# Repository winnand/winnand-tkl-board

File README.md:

# The Winnand TKL Keyboard

This project is a custom keyboard based off of JoeScotto's guides from YouTube. It is a standard TKL Board which replaces the Pause key with a rotary encoder. It uses QMK with Vial support for on-the-go layout customization.

I made this project because I enjoyed the idea of having a keyboard that I made myself, with the features and rigidity of a top-of-the-line keyboard. I hoped that it would teach me more about firmware and microcontrollers for future projects, and have a good keyboard that I would be able to use for many years to come. 

# BOM

|Part #                                    |Min. Quantity |Name on Seller Website                                                                                                          |Description      |Link                                                  |Color/Size                                                 |Quantity|Unit Price ($)|Total Price ($)|Running Total ($)|
|------------------------------------------|--------------|--------------------------------------------------------------------------------------------------------------------------------|-----------------|------------------------------------------------------|-----------------------------------------------------------|--------|--------------|---------------|-----------------|
|MX-keyboard switches                      |86            |Outemu Switch Mechanical Keyboard Switch 3Pin Clicky Linear Tactile Silent Switches RGB LED SMD Gaming Compatible With MX Switch|Keyboard Switches|https://www.aliexpress.us/item/3256802192387196.html  |Color: Dust-Proof Purple Axis Body: 90PCS                  |1       |$10.31        |$10.31         |$10.31           |
|Red LED                                   |87            |100pcs 5mm LED Diode F5 Assorted Kit White Green Red Blue Yellow Orange Pink Purple Warm White DIY Light Emitting Diode         |Diodes           |https://www.aliexpress.us/item/3256806276743323.html  |Color: Red-Red                                             |1       |$2.19         |$2.19          |$12.50           |
|EC11 Rotary Encoder                       |1             |5PCS/LOT 20 Position 360 Degree Rotary Encoder EC11 w Push Button 5Pin Handle Long 15/20MM With A Built In Push Button Switch   |Rotary Encoder   |https://www.aliexpress.us/item/3256805796819763.html? |15MM Half handle                                           |1       |$3.30         |$3.30          |$15.80           |
|Raspberry Pi Pico                         |1             |Raspberry Pi Pico                                                                                                               |Microcontroller  |https://www.sparkfun.com/raspberry-pi-pico.html       |                                                           |0       |$4.60         |$0.00          |$15.80           |
|Micro USB male to panel mount USB C female|1             |USB 3.1 Type C Micro Usb2.0 With Panel Mount Screw Extension Cable Cord USB C Male To Female Extending Wire Extender Data Cord  |Adapter Cable    |https://www.aliexpress.us/item/3256806244885684.html  |A3                                                         |1       |$2.69         |$2.69          |$18.49           |
|M2 x 6mm Button Head screw                |11            |10/50pcs M1.6 M2 M2.5 M3 M4 M5 M6 M8 Black Grade 10.9 Steel ISO7380 Hexagon Hex Socket Head Button Mushroom Allen Bolt Screw    |Mounting Screws  |https://www.aliexpress.us/item/2251832782727837.html  |Size: M2 (50pcs) Length: 6mm                               |1       |$1.07         |$1.07          |$19.56           |
|MX Keycaps                                |TKL Layout    |104pcs ABS Universal Mechanical Keyboard Keycaps Ergonomic Blank Keycaps For Cherry MX Keyboard Replacement OEM Backlit Key Cap |Keycaps          |https://www.aliexpress.us/item/3256808802544300.html  |Red black                                                  |1       |$11.48        |$11.48         |$31.04           |
|Plate Mount Stabilizers                   |1x 6.25U 4x 2U|KEYCOOL V3 PCB Plate Mounted Stabilizer for Gaming Mechanical Keyboard Lubrication Satellite Switches for 1.2mm 1.6mm PCB 6.25U |Stabilizers      |https://www.aliexpress.us/item/3256808467378574.html  |Black 4 in 1                                               |1       |$3.01         |$3.01          |$34.05           |
|M2, OD4mm Heatset Inserts                 |11            |M2 M2.5 M3 M4 M5 M6 Brass Hot Melt Insert Knurled Nut Thread Heat Molding Double Twill Injection Embedment Nut For 3D Printer   |Heatset Inserts  |https://www.aliexpress.us/item/3256803396040989.html  |Size: M2(OD4mm)  Color: Length 5mm 50pcs                   |1       |$2.27         |$2.27          |$36.32           |
|Winnand-TKL PCB                           |1             |JLCPCB                                                                                                                          |PCB              |https://cart.jlcpcb.com/quote?spm=Jlcpcb.Homepage.1006|Defaults except: PCB Color: Black Via Covering: Untented   |5       |$4.16         |$20.80         |$57.12           |
|ARGB lights                               |1             |Addressable ARGB 5V LED Strip 3Pin Computer PC Case Tape Light WS2812B SMD 5050 Flexible Changeable Color Gamer Desktop Lamp    |Lights           |https://www.aliexpress.us/item/3256802938234249.html? |Emitting Color: 1 x 0.5m 30leds  Color: IP30 Non waterproof|1       |$4.00         |$4.00          |$61.12           |

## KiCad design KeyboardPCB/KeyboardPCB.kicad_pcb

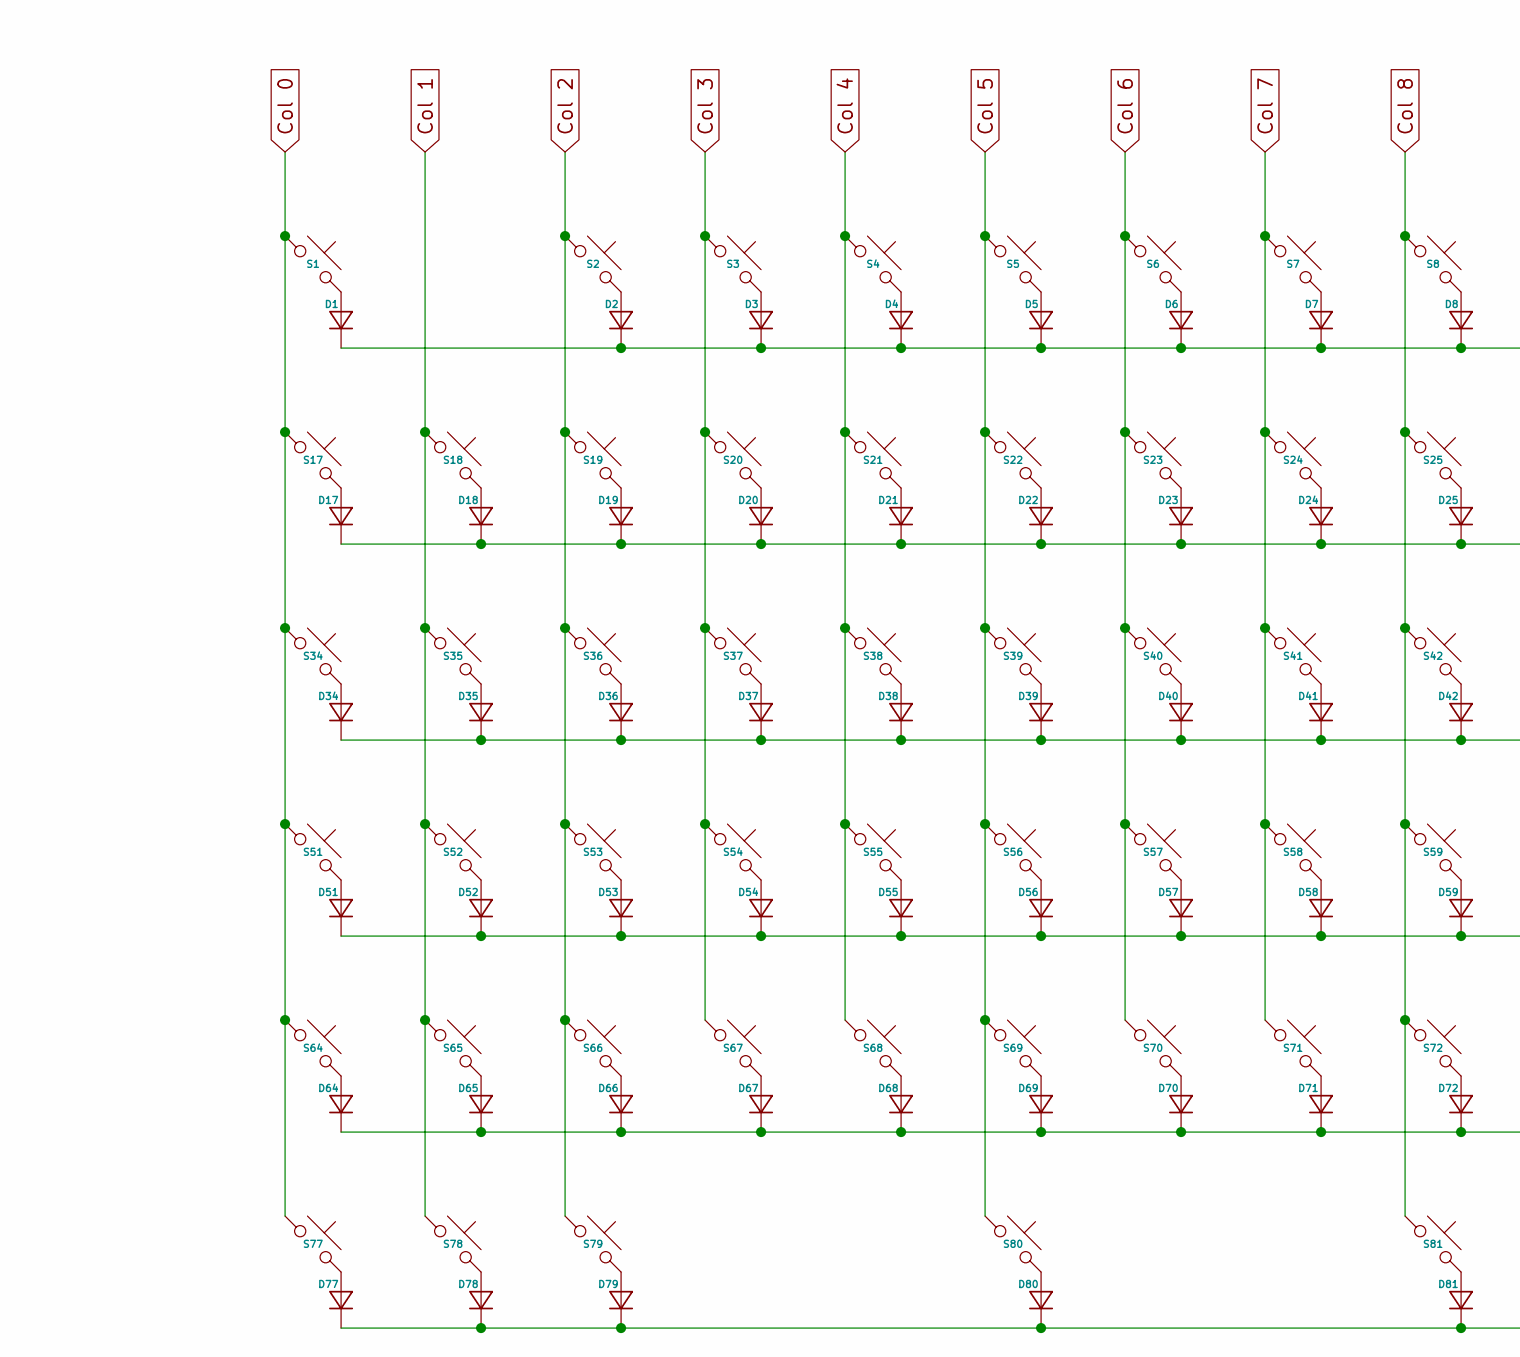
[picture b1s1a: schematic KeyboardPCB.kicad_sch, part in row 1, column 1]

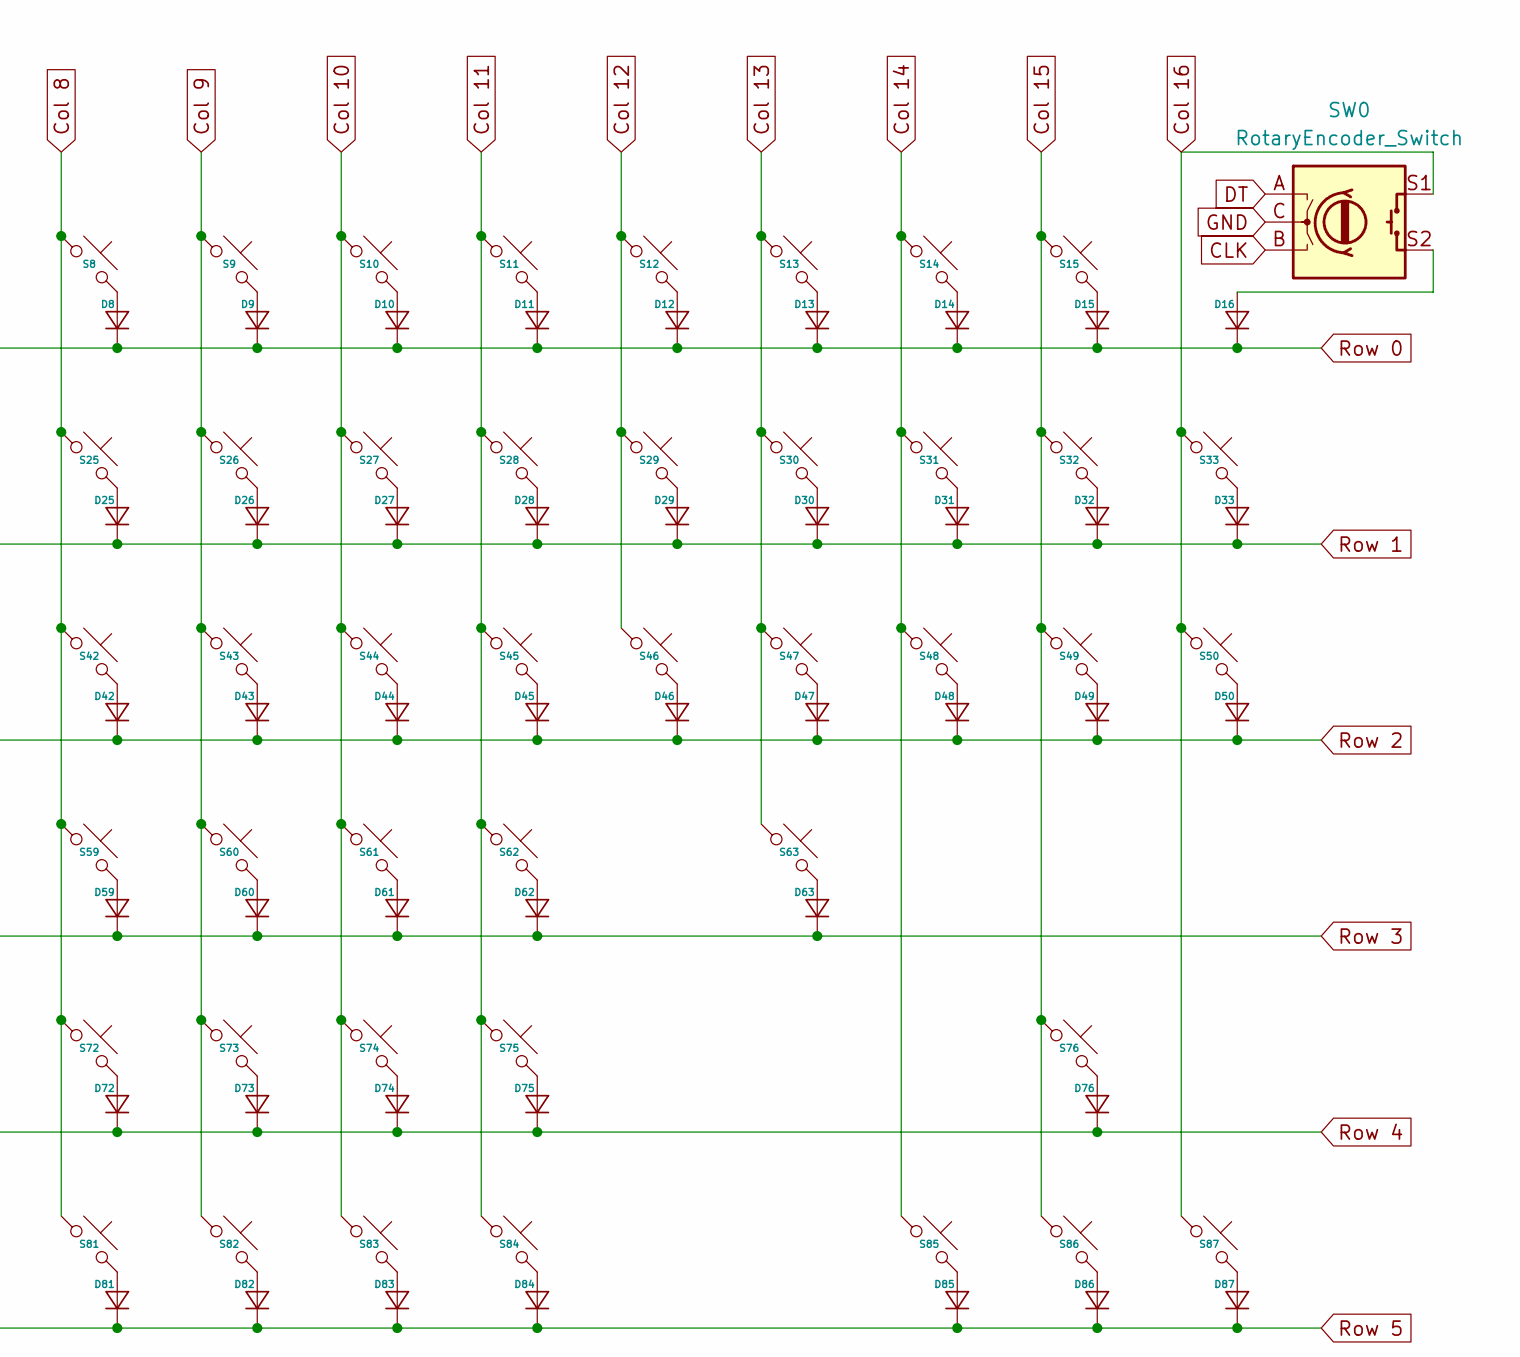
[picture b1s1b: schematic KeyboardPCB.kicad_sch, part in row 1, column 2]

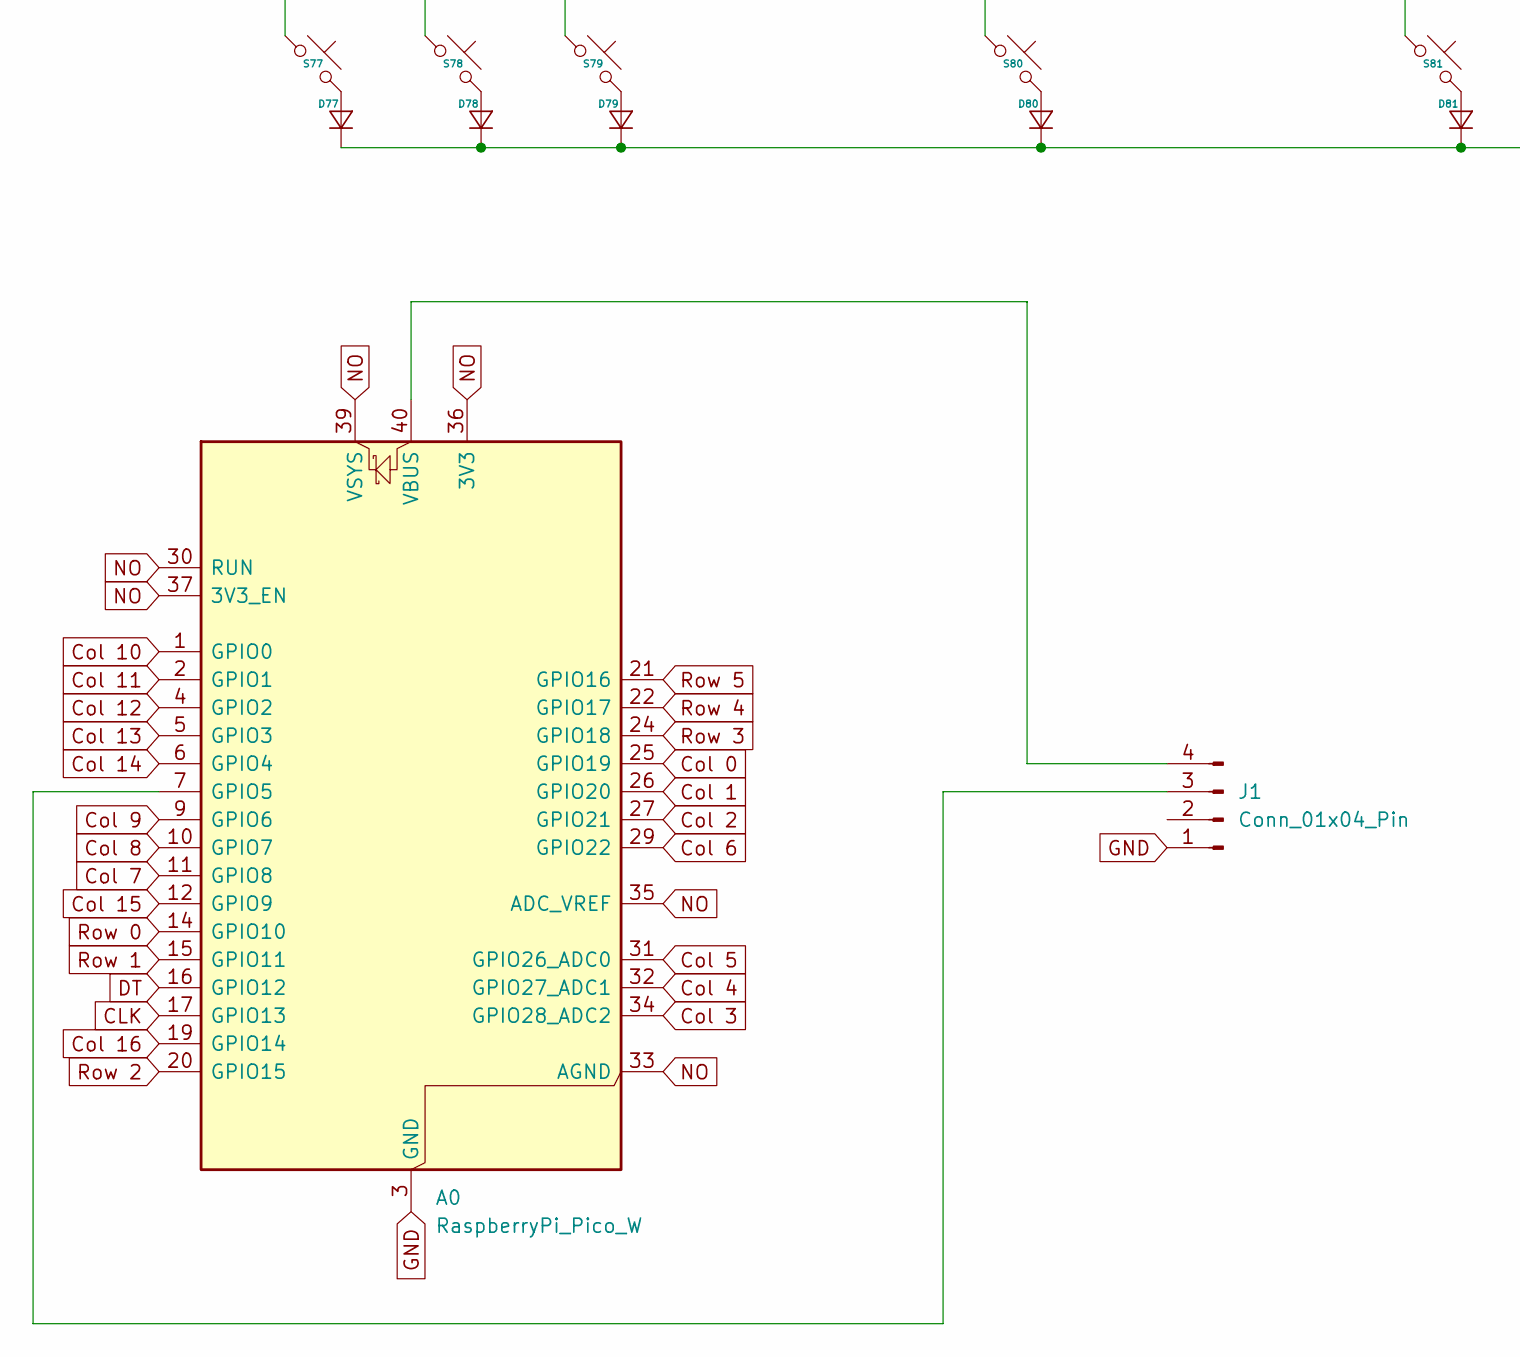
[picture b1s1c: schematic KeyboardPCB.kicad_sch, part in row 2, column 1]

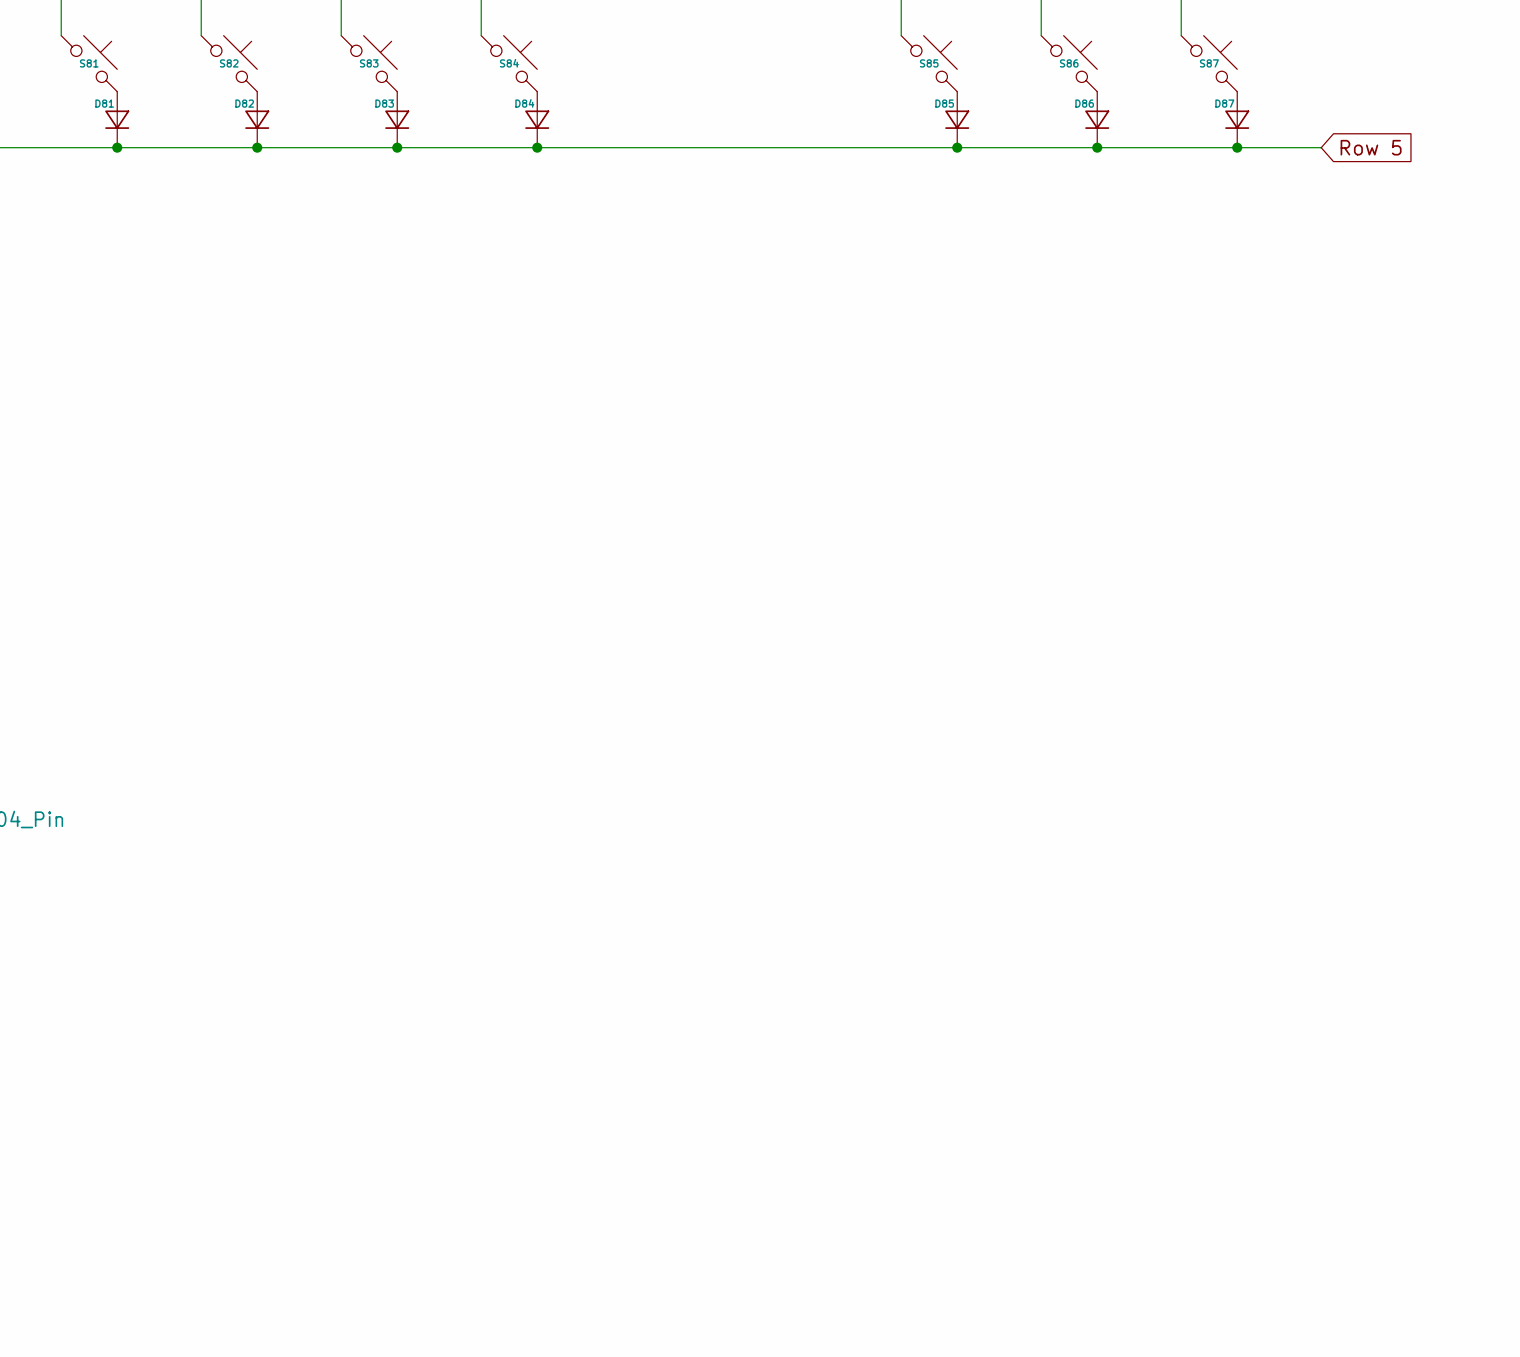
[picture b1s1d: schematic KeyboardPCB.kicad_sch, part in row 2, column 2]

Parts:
A0: RaspberryPi_Pico_W; RaspberryPi_Pico_W_SMD_HandSolder
D1, D2, D3, D4, D5, D6, D7, D8, D9, D10, D11, D12, D13, D14, D15, D16, D17, D18, D19, D20, D21, D22, D23, D24, D25, D26, D27, D28, D29, D30, D31, D32, D33, D34, D35, D36, D37, D38, D39, D40, D41, D42, D43, D44, D45, D46, D47, D48, D49, D50, D51, D52, D53, D54, D55, D56, D57, D58, D59, D60, D61, D62, D63, D64, D65, D66, D67, D68, D69, D70, D71, D72, D73, D74, D75, D76, D77, D78, D79, D80, D81, D82, D83, D84, D85, D86, D87: Diode_DO-35
J1: Conn_01x04_Pin; PinHeader_1x04_P2.54mm_Vertical
S1, S2, S3, S4, S5, S6, S7, S8, S9, S10, S11, S12, S13, S14, S15, S17, S18, S19, S20, S21, S22, S23, S24, S25, S26, S27, S28, S29, S31, S32, S33, S35, S36, S37, S38, S39, S40, S41, S42, S43, S44, S45, S46, S48, S49, S50, S52, S53, S54, S55, S56, S57, S58, S59, S60, S61, S62, S65, S66, S67, S68, S69, S70, S71, S72, S73, S74, S76, S85, S86, S87: MX_PCB_1.00u
S30: MX_PCB_2.00u
S34, S47: MX_PCB_1.50u
S51: MX_PCB_1.75u
S63, S64: MX_PCB_2.25u
S75: MX_PCB_2.75u
S77, S78, S79, S81, S82, S83, S84: MX_PCB_1.25u
S80: MX_PCB_6.25u
SW0: RotaryEncoder_Switch; Encoder_EC11_MX

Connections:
CLK: A0.17 (GPIO13), SW0.B
Col 0: A0.25 (GPIO19), S1.1, S17.1, S34.1, S51.1, S64.1, S77.1
Col 1: A0.26 (GPIO20), S18.1, S35.1, S52.1, S65.1, S78.1
Col 2: A0.27 (GPIO21), S2.1, S19.1, S36.1, S53.1, S66.1, S79.1
Col 3: A0.34 (GPIO28_ADC2), S3.1, S20.1, S37.1, S54.1, S67.1
Col 4: A0.32 (GPIO27_ADC1), S4.1, S21.1, S38.1, S55.1, S68.1
Col 5: A0.31 (GPIO26_ADC0), S5.1, S22.1, S39.1, S56.1, S69.1, S80.1
Col 6: A0.29 (GPIO22), S6.1, S23.1, S40.1, S57.1, S70.1
Col 7: A0.11 (GPIO8), S7.1, S24.1, S41.1, S58.1, S71.1
Col 8: A0.10 (GPIO7), S8.1, S25.1, S42.1, S59.1, S72.1, S81.1
Col 9: A0.9 (GPIO6), S9.1, S26.1, S43.1, S60.1, S73.1, S82.1
Col 10: A0.1 (GPIO0), S10.1, S27.1, S44.1, S61.1, S74.1, S83.1
Col 11: A0.2 (GPIO1), S11.1, S28.1, S45.1, S62.1, S75.1, S84.1
Col 12: A0.4 (GPIO2), S12.1, S29.1, S46.1
Col 13: A0.5 (GPIO3), S13.1, S30.1, S47.1, S63.1
Col 14: A0.6 (GPIO4), S14.1, S31.1, S48.1, S85.1
Col 15: A0.12 (GPIO9), S15.1, S32.1, S49.1, S76.1, S86.1
Col 16: A0.19 (GPIO14), S33.1, S50.1, S87.1, SW0.S1
DT: A0.16 (GPIO12), SW0.A
GND: A0.3 (GND), A0.8 (GND), A0.13 (GND), A0.18 (GND), A0.23 (GND), A0.28 (GND), A0.38 (GND), J1.1, SW0.C
NO: A0.30 (RUN), A0.33 (AGND), A0.35 (ADC_VREF), A0.36 (3V3), A0.37 (3V3_EN), A0.39 (VSYS)
unnamed: A0.7 (GPIO5), J1.3
unnamed: A0.40 (VBUS), J1.4
unnamed: D1.2 (A), S1.2
unnamed: D2.2 (A), S2.2
unnamed: D3.2 (A), S3.2
unnamed: D4.2 (A), S4.2
unnamed: D5.2 (A), S5.2
unnamed: D6.2 (A), S6.2
unnamed: D7.2 (A), S7.2
unnamed: D8.2 (A), S8.2
unnamed: D9.2 (A), S9.2
unnamed: D10.2 (A), S10.2
unnamed: D11.2 (A), S11.2
unnamed: D12.2 (A), S12.2
unnamed: D13.2 (A), S13.2
unnamed: D14.2 (A), S14.2
unnamed: D15.2 (A), S15.2
unnamed: D16.2 (A), SW0.S2
unnamed: D17.2 (A), S17.2
unnamed: D18.2 (A), S18.2
unnamed: D19.2 (A), S19.2
unnamed: D20.2 (A), S20.2
unnamed: D21.2 (A), S21.2
unnamed: D22.2 (A), S22.2
unnamed: D23.2 (A), S23.2
unnamed: D24.2 (A), S24.2
unnamed: D25.2 (A), S25.2
unnamed: D26.2 (A), S26.2
unnamed: D27.2 (A), S27.2
unnamed: D28.2 (A), S28.2
unnamed: D29.2 (A), S29.2
unnamed: D30.2 (A), S30.2
unnamed: D31.2 (A), S31.2
unnamed: D32.2 (A), S32.2
unnamed: D33.2 (A), S33.2
unnamed: D34.2 (A), S34.2
unnamed: D35.2 (A), S35.2
unnamed: D36.2 (A), S36.2
unnamed: D37.2 (A), S37.2
unnamed: D38.2 (A), S38.2
unnamed: D39.2 (A), S39.2
unnamed: D40.2 (A), S40.2
unnamed: D41.2 (A), S41.2
unnamed: D42.2 (A), S42.2
unnamed: D43.2 (A), S43.2
unnamed: D44.2 (A), S44.2
unnamed: D45.2 (A), S45.2
unnamed: D46.2 (A), S46.2
unnamed: D47.2 (A), S47.2
unnamed: D48.2 (A), S48.2
unnamed: D49.2 (A), S49.2
unnamed: D50.2 (A), S50.2
unnamed: D51.2 (A), S51.2
unnamed: D52.2 (A), S52.2
unnamed: D53.2 (A), S53.2
unnamed: D54.2 (A), S54.2
unnamed: D55.2 (A), S55.2
unnamed: D56.2 (A), S56.2
unnamed: D57.2 (A), S57.2
unnamed: D58.2 (A), S58.2
unnamed: D59.2 (A), S59.2
unnamed: D60.2 (A), S60.2
unnamed: D61.2 (A), S61.2
unnamed: D62.2 (A), S62.2
unnamed: D63.2 (A), S63.2
unnamed: D64.2 (A), S64.2
unnamed: D65.2 (A), S65.2
unnamed: D66.2 (A), S66.2
unnamed: D67.2 (A), S67.2
unnamed: D68.2 (A), S68.2
unnamed: D69.2 (A), S69.2
unnamed: D70.2 (A), S70.2
unnamed: D71.2 (A), S71.2
unnamed: D72.2 (A), S72.2
unnamed: D73.2 (A), S73.2
unnamed: D74.2 (A), S74.2
unnamed: D75.2 (A), S75.2
unnamed: D76.2 (A), S76.2
unnamed: D77.2 (A), S77.2
unnamed: D78.2 (A), S78.2
unnamed: D79.2 (A), S79.2
unnamed: D80.2 (A), S80.2
unnamed: D81.2 (A), S81.2
unnamed: D82.2 (A), S82.2
unnamed: D83.2 (A), S83.2
unnamed: D84.2 (A), S84.2
unnamed: D85.2 (A), S85.2
unnamed: D86.2 (A), S86.2
unnamed: D87.2 (A), S87.2
Row 0: A0.14 (GPIO10), D1.1 (K), D2.1 (K), D3.1 (K), D4.1 (K), D5.1 (K), D6.1 (K), D7.1 (K), D8.1 (K), D9.1 (K), D10.1 (K), D11.1 (K), D12.1 (K), D13.1 (K), D14.1 (K), D15.1 (K), D16.1 (K)
Row 1: A0.15 (GPIO11), D17.1 (K), D18.1 (K), D19.1 (K), D20.1 (K), D21.1 (K), D22.1 (K), D23.1 (K), D24.1 (K), D25.1 (K), D26.1 (K), D27.1 (K), D28.1 (K), D29.1 (K), D30.1 (K), D31.1 (K), D32.1 (K), D33.1 (K)
Row 2: A0.20 (GPIO15), D34.1 (K), D35.1 (K), D36.1 (K), D37.1 (K), D38.1 (K), D39.1 (K), D40.1 (K), D41.1 (K), D42.1 (K), D43.1 (K), D44.1 (K), D45.1 (K), D46.1 (K), D47.1 (K), D48.1 (K), D49.1 (K), D50.1 (K)
Row 3: A0.24 (GPIO18), D51.1 (K), D52.1 (K), D53.1 (K), D54.1 (K), D55.1 (K), D56.1 (K), D57.1 (K), D58.1 (K), D59.1 (K), D60.1 (K), D61.1 (K), D62.1 (K), D63.1 (K)
Row 4: A0.22 (GPIO17), D64.1 (K), D65.1 (K), D66.1 (K), D67.1 (K), D68.1 (K), D69.1 (K), D70.1 (K), D71.1 (K), D72.1 (K), D73.1 (K), D74.1 (K), D75.1 (K), D76.1 (K)
Row 5: A0.21 (GPIO16), D77.1 (K), D78.1 (K), D79.1 (K), D80.1 (K), D81.1 (K), D82.1 (K), D83.1 (K), D84.1 (K), D85.1 (K), D86.1 (K), D87.1 (K)

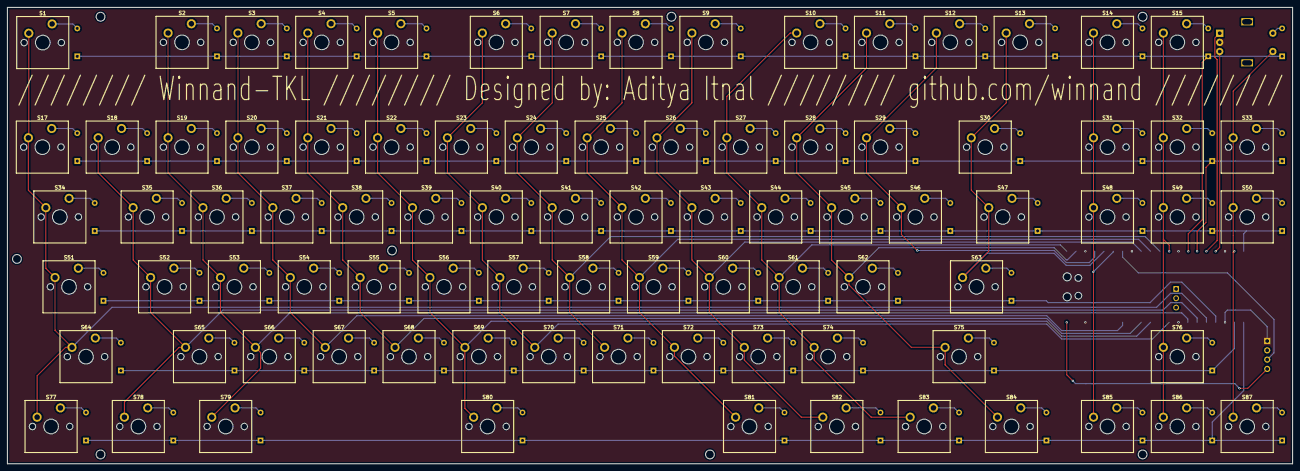
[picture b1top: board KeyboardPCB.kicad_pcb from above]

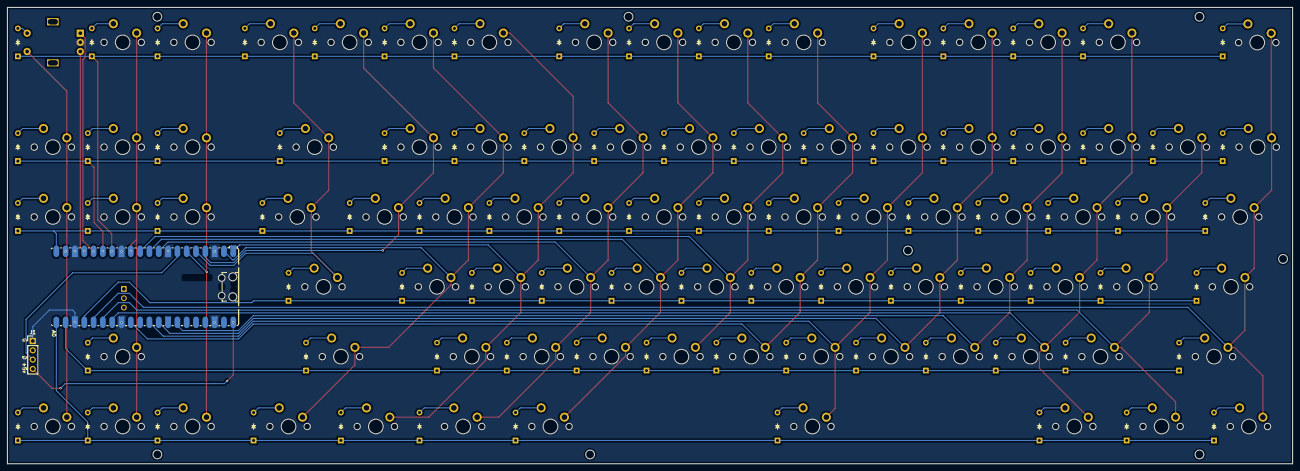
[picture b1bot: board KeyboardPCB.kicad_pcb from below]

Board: 2 copper layers, 350.5 x 124.5 mm, 176 parts (89 on the bottom side), 116 nets.

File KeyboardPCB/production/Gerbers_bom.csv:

Designator,Footprint,Quantity,Value,LCSC Part #
A0,RaspberryPi_Pico_W_SMD_HandSolder,1,RaspberryPi_Pico_W,
"D1, D10, D11, D12, D13, D14, D15, D16, D17, D18, D19, D2, D20, D21, D22, D23, D24, D25, D26, D27, D28, D29, D3, D30, D31, D32, D33, D34, D35, D36, D37, D38, D39, D4, D40, D41, D42, D43, D44, D45, D46, D47, D48, D49, D5, D50, D51, D52, D53, D54, D55, D56, D57, D58, D59, D6, D60, D61, D62, D63, D64, D65, D66, D67, D68, D69, D7, D70, D71, D72, D73, D74, D75, D76, D77, D78, D79, D8, D80, D81, D82, D83, D84, D85, D86, D87, D9",Diode_DO-35,87,~,
J1,PinHeader_1x04_P2.54mm_Vertical,1,Conn_01x04_Pin,
"S1, S10, S11, S12, S13, S14, S15, S17, S18, S19, S2, S20, S21, S22, S23, S24, S25, S26, S27, S28, S29, S3, S31, S32, S33, S35, S36, S37, S38, S39, S4, S40, S41, S42, S43, S44, S45, S46, S48, S49, S5, S50, S52, S53, S54, S55, S56, S57, S58, S59, S6, S60, S61, S62, S65, S66, S67, S68, S69, S7, S70, S71, S72, S73, S74, S76, S8, S85, S86, S87, S9",MX_PCB_1.00u,71,~,
S30,MX_PCB_2.00u,1,~,
"S34, S47",MX_PCB_1.50u,2,~,
S51,MX_PCB_1.75u,1,~,
"S63, S64",MX_PCB_2.25u,2,~,
S75,MX_PCB_2.75u,1,~,
"S77, S78, S79, S81, S82, S83, S84",MX_PCB_1.25u,7,~,
S80,MX_PCB_6.25u,1,~,
SW0,Encoder_EC11_MX,1,RotaryEncoder_Switch,

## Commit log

2025-12-10 Schematic and initial PCB design
2025-12-11 Finished PCB v1
2025-12-22 CAD Files
2025-12-22 Keyboard Case Master Fusion File
2025-12-22 updated README and BOM
2025-12-26 Added Firmware files
2025-12-28 added RGB header
2025-12-28 added rgb to the BOM
2026-01-18 Added per-key LED lighting
